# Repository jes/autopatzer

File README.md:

# autopatzer

An automatic chess board, supporting online play with people all over the world via the [Lichess Boards API](https://lichess.org/blog/XlRW5REAAB8AUJJ-/welcome-lichess-boards).

This repo contains FreeCAD files for the mechanical design, KiCad files for PCB design, Arduino code to run on
the microcontroller, Perl code for the library/program that interfaces with the controller, and JavaScript code for the
user interface and Lichess interface.

You can [watch a video of the board](https://www.youtube.com/watch?v=8ScFtkWvHW8) if you want.

## Build one yourself

I thoroughly encourage you to build an Autopatzer board. You'll need:

 - 3d printer
 - soldering skills
 - general DIY skills
 - and it would probably help to have prior experience with Arduino and Raspberry Pi

There aren't currently a decent set of instructions, so if you want to build one let's try and write some
instructions as you go so that it might be easier for whoever comes next!

There are some notes about how you might want to change the design in my blog post: https://incoherency.co.uk/blog/stories/autopatzer.html

## Architecture

There is a NEMA17 stepper motor for each of the X and Y axis, from an old 3d printer. The stepper motors are controlled by A4988 stepper
motor drivers, which are controlled using the step/direction pins, driven by the AccelStepper Arduino library. The electromagnet is switched
on and off with a MOSFET. The pieces are detected with an analogue hall effect sensor under each square. These 64 analogue signals are reduced
to 8 signals with 8x CD4051 8-to-1 analogue multiplexers. All of the code for this runs on a Teensy 3.2 microcontroller, and the rest is
adequately explained by this diagram:

## Contact

The Electron app providing the user interface is by Miles Armstrong: miles@milesarmstrong.co.uk

The rest is by James Stanley: james@incoherency.co.uk

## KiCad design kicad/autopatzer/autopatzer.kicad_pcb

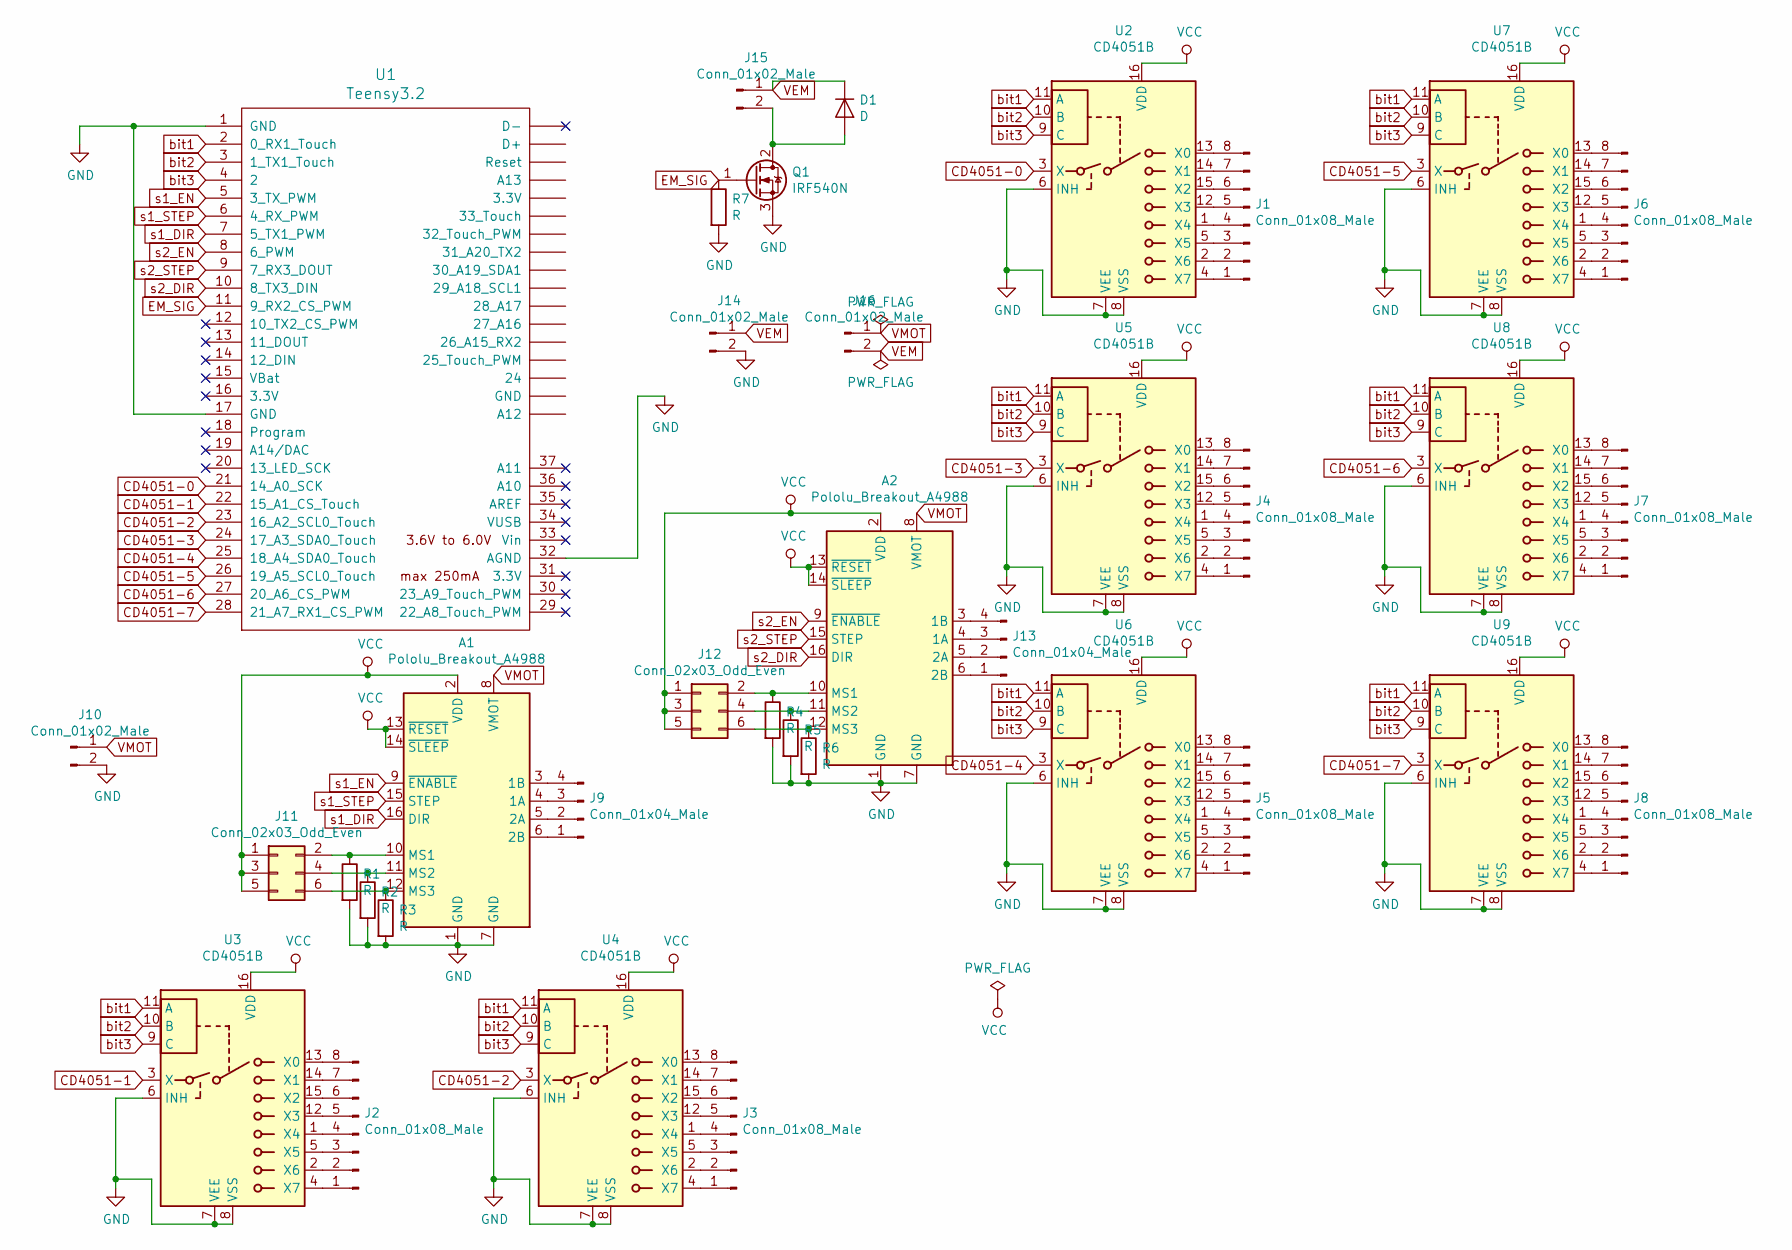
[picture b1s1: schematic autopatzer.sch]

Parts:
A1, A2: Pololu_Breakout_A4988; Pololu_Breakout-16_15.2x20.3mm
D1: D; D_5W_P12.70mm_Horizontal
J1, J2, J3, J4, J5, J6, J7, J8: Conn_01x08_Male; PinHeader_1x08_P2.54mm_Vertical
J9, J13: Conn_01x04_Male; PinHeader_1x04_P2.54mm_Vertical
J10, J14, J15, J16: Conn_01x02_Male; PinHeader_1x02_P2.54mm_Vertical
J11, J12: Conn_02x03_Odd_Even; PinHeader_2x03_P2.54mm_Vertical
Q1: IRF540N; TO-220-3_Vertical
R1, R2, R3, R4, R5, R6, R7: R; R_Axial_DIN0411_L9.9mm_D3.6mm_P12.70mm_Horizontal
U1: Teensy3.2; Teensy30_31_32_LC
U2, U3, U4, U5, U6, U7, U8, U9: CD4051B; DIP-16_W7.62mm

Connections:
CD4051-0: U1.21 (14_A0_SCK), U2.3 (X)
CD4051-1: U1.22 (15_A1_CS_Touch), U3.3 (X)
CD4051-2: U1.23 (16_A2_SCL0_Touch), U4.3 (X)
CD4051-3: U1.24 (17_A3_SDA0_Touch), U5.3 (X)
CD4051-4: U1.25 (18_A4_SDA0_Touch), U6.3 (X)
CD4051-5: U1.26 (19_A5_SCL0_Touch), U7.3 (X)
CD4051-6: U1.27 (20_A6_CS_PWM), U8.3 (X)
CD4051-7: U1.28 (21_A7_RX1_CS_PWM), U9.3 (X)
EM_SIG: Q1.1 (G), R7.1, U1.11 (9_RX2_CS_PWM)
GND: A1.1 (GND), A1.7 (GND), A2.1 (GND), A2.7 (GND), J10.2, J14.2, Q1.3 (S), R1.2, R2.2, R3.2, R4.2, R5.2, R6.2, R7.2, U1.1 (GND), U1.17 (GND), U1.32 (AGND), U2.6 (INH), U2.7 (VEE), U2.8 (VSS), U3.6 (INH), U3.7 (VEE), U3.8 (VSS), U4.6 (INH), U4.7 (VEE), U4.8 (VSS), U5.6 (INH), U5.7 (VEE), U5.8 (VSS), U6.6 (INH), U6.7 (VEE), U6.8 (VSS), U7.6 (INH), U7.7 (VEE), U7.8 (VSS), U8.6 (INH), U8.7 (VEE), U8.8 (VSS), U9.6 (INH), U9.7 (VEE), U9.8 (VSS)
unnamed: A1.3 (1B), J9.4
unnamed: A1.4 (1A), J9.3
unnamed: A1.5 (2A), J9.2
unnamed: A1.6 (2B), J9.1
unnamed: A1.10 (MS1), J11.2, R1.1
unnamed: A1.11 (MS2), J11.4, R2.1
unnamed: A1.12 (MS3), J11.6, R3.1
unnamed: A2.3 (1B), J13.4
unnamed: A2.4 (1A), J13.3
unnamed: A2.5 (2A), J13.2
unnamed: A2.6 (2B), J13.1
unnamed: A2.10 (MS1), J12.2, R4.1
unnamed: A2.11 (MS2), J12.4, R5.1
unnamed: A2.12 (MS3), J12.6, R6.1
unnamed: D1.2 (A), J15.2, Q1.2 (D)
unnamed: J1.1, U2.4 (X7)
unnamed: J1.2, U2.2 (X6)
unnamed: J1.3, U2.5 (X5)
unnamed: J1.4, U2.1 (X4)
unnamed: J1.5, U2.12 (X3)
unnamed: J1.6, U2.15 (X2)
unnamed: J1.7, U2.14 (X1)
unnamed: J1.8, U2.13 (X0)
unnamed: J2.1, U3.4 (X7)
unnamed: J2.2, U3.2 (X6)
unnamed: J2.3, U3.5 (X5)
unnamed: J2.4, U3.1 (X4)
unnamed: J2.5, U3.12 (X3)
unnamed: J2.6, U3.15 (X2)
unnamed: J2.7, U3.14 (X1)
unnamed: J2.8, U3.13 (X0)
unnamed: J3.1, U4.4 (X7)
unnamed: J3.2, U4.2 (X6)
unnamed: J3.3, U4.5 (X5)
unnamed: J3.4, U4.1 (X4)
unnamed: J3.5, U4.12 (X3)
unnamed: J3.6, U4.15 (X2)
unnamed: J3.7, U4.14 (X1)
unnamed: J3.8, U4.13 (X0)
unnamed: J4.1, U5.4 (X7)
unnamed: J4.2, U5.2 (X6)
unnamed: J4.3, U5.5 (X5)
unnamed: J4.4, U5.1 (X4)
unnamed: J4.5, U5.12 (X3)
unnamed: J4.6, U5.15 (X2)
unnamed: J4.7, U5.14 (X1)
unnamed: J4.8, U5.13 (X0)
unnamed: J5.1, U6.4 (X7)
unnamed: J5.2, U6.2 (X6)
unnamed: J5.3, U6.5 (X5)
unnamed: J5.4, U6.1 (X4)
unnamed: J5.5, U6.12 (X3)
unnamed: J5.6, U6.15 (X2)
unnamed: J5.7, U6.14 (X1)
unnamed: J5.8, U6.13 (X0)
unnamed: J6.1, U7.4 (X7)
unnamed: J6.2, U7.2 (X6)
unnamed: J6.3, U7.5 (X5)
unnamed: J6.4, U7.1 (X4)
unnamed: J6.5, U7.12 (X3)
unnamed: J6.6, U7.15 (X2)
unnamed: J6.7, U7.14 (X1)
unnamed: J6.8, U7.13 (X0)
unnamed: J7.1, U8.4 (X7)
unnamed: J7.2, U8.2 (X6)
unnamed: J7.3, U8.5 (X5)
unnamed: J7.4, U8.1 (X4)
unnamed: J7.5, U8.12 (X3)
unnamed: J7.6, U8.15 (X2)
unnamed: J7.7, U8.14 (X1)
unnamed: J7.8, U8.13 (X0)
unnamed: J8.1, U9.4 (X7)
unnamed: J8.2, U9.2 (X6)
unnamed: J8.3, U9.5 (X5)
unnamed: J8.4, U9.1 (X4)
unnamed: J8.5, U9.12 (X3)
unnamed: J8.6, U9.15 (X2)
unnamed: J8.7, U9.14 (X1)
unnamed: J8.8, U9.13 (X0)
VCC: A1.2 (VDD), A1.13 (~RESET), A1.14 (~SLEEP), A2.2 (VDD), A2.13 (~RESET), A2.14 (~SLEEP), J11.1, J11.3, J11.5, J12.1, J12.3, J12.5, U2.16 (VDD), U3.16 (VDD), U4.16 (VDD), U5.16 (VDD), U6.16 (VDD), U7.16 (VDD), U8.16 (VDD), U9.16 (VDD)
VEM: D1.1 (K), J14.1, J15.1, J16.2
VMOT: A1.8 (VMOT), A2.8 (VMOT), J10.1, J16.1
bit1: U1.2 (0_RX1_Touch), U2.11 (A), U3.11 (A), U4.11 (A), U5.11 (A), U6.11 (A), U7.11 (A), U8.11 (A), U9.11 (A)
bit2: U1.3 (1_TX1_Touch), U2.10 (B), U3.10 (B), U4.10 (B), U5.10 (B), U6.10 (B), U7.10 (B), U8.10 (B), U9.10 (B)
bit3: U1.4 (2), U2.9 (C), U3.9 (C), U4.9 (C), U5.9 (C), U6.9 (C), U7.9 (C), U8.9 (C), U9.9 (C)
s1_DIR: A1.16 (DIR), U1.7 (5_TX1_PWM)
s1_EN: A1.9 (~ENABLE), U1.5 (3_TX_PWM)
s1_STEP: A1.15 (STEP), U1.6 (4_RX_PWM)
s2_DIR: A2.16 (DIR), U1.10 (8_TX3_DIN)
s2_EN: A2.9 (~ENABLE), U1.8 (6_PWM)
s2_STEP: A2.15 (STEP), U1.9 (7_RX3_DOUT)

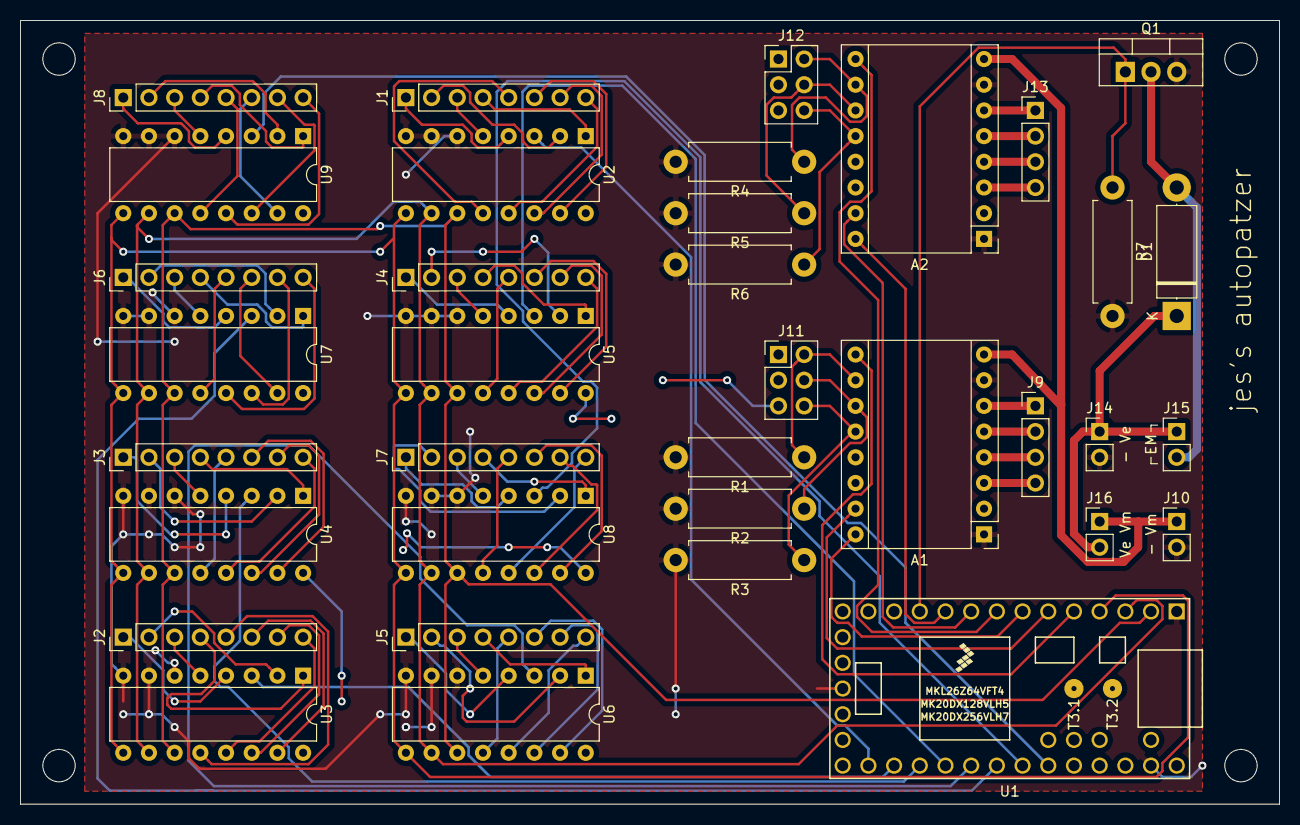
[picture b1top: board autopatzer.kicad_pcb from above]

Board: 2 copper layers, 124.5 x 77.5 mm, 36 parts (0 on the bottom side), 101 nets.

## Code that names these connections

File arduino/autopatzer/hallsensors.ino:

/* Hall sensor code for autopatzer
 *  
 * James Stanley 2020
 */

const int pieceSettleMs = 50; // don't report a square changed until it has settled for N ms

bool squareOccupied[64];
bool realSquareOccupied[64];
unsigned long lastChange[64];

// map sensor locations to actual squares (0=a1, 7=a8, 8=b1, 56=h1, 63=h8)
int squareMap[64] = {
  36, 29, 18, 43, 59, 12, 49,  4,
  32, 31, 21, 45, 61, 15, 52,  0,
  34, 26, 20, 42, 56,  9, 54,  2,
  38, 24, 16, 44, 60, 11, 50,  5,
  35, 27, 17, 40, 58, 10, 53,  7,
  37, 30, 19, 47, 63, 13, 55,  6,
  39, 28, 23, 46, 62,  8, 51,  3,
  33, 25, 22, 41, 57, 14, 48,  1,
};

// we set a different threshold for each square
int analogThreshold[64] = {
//  1    2    3    4    5    6    7    8
  715, 745, 695, 705, 690, 650, 690, 730, // a
  715, 680, 715, 735, 675, 725, 675, 730, // b
  740, 705, 695, 655, 680, 710, 730, 715, // c
  720, 690, 740, 720, 705, 690, 640, 715, // d
  710, 755, 670, 695, 640, 710, 715, 750, // e
  700, 745, 675, 705, 725, 690, 715, 705, // f
  660, 700, 630, 645, 710, 725, 720, 725, // g
  725, 675, 690, 680, 720, 675, 680, 710, // h
};

int bit1pin, bit2pin, bit3pin;

void initHallSensors(int bit1, int bit2, int bit3) {
  bit1pin = bit1;
  bit2pin = bit2;
  bit3pin = bit3;
  pinMode(bit1, OUTPUT);
  pinMode(bit2, OUTPUT);
  pinMode(bit3, OUTPUT);

  scanHallSensors();
  for (int i = 0; i < 64; i++)
    realSquareOccupied[i] = squareOccupied[i];
}

void waitHallSensors(int ms) {
  unsigned long start = millis();

  while (millis() < start+ms) {
    updateHallSensors();
  }
}

void updateHallSensors() {
  scanHallSensors();
  for (int i = 0; i < 64; i++) {
    if (millis() - lastChange[i] > pieceSettleMs && squareOccupied[i] != realSquareOccupied[i]) {
      realSquareOccupied[i] = squareOccupied[i];
      if (realSquareOccupied[i] ) {
        Serial.print("piecedown "); Serial.println(square2Name(i));
      } else {
        Serial.print("pieceup "); Serial.println(square2Name(i));
      }
    }
  }
}

void scanHallSensors() {
  for (int i = 0; i < 8; i++) {
    digitalWrite(bit1pin, i&1);
    digitalWrite(bit2pin, i&2);
    digitalWrite(bit3pin, i&4);
    // XXX: do we need to wait between writing to the bit pins and reading from the analogue pins?
    for (int j = 0; j < 8; j++) {
      updateSteppers(); // HACK: don't let scanHallSensors() block stepper motor operation
      int sqr = squareMap[i*8+j];
      int val = analogRead(j);
      bool occ = val > (analogThreshold[sqr] + 35);
      if (squareOccupied[sqr] != occ) {
        squareOccupied[sqr] = occ;
        lastChange[sqr] = millis();
      }
    }
  }
}

void analogScanHallSensors() {
  int maxRead[64];
  for (int i = 0; i < 64; i++)
    maxRead[i] = 0;
  for (int n = 0; n < 100; n++) {
  for (int i = 0; i < 8; i++) {
    digitalWrite(bit1pin, i&1);
    digitalWrite(bit2pin, i&2);
    digitalWrite(bit3pin, i&4);
    // XXX: do we need to wait between writing to the bit pins and reading from the analogue pins?
    for (int j = 0; j < 8; j++) {
      int sqr = squareMap[i*8+j];
      int val = analogRead(j);
      if (val > maxRead[sqr])
        maxRead[sqr] = val;
    }
  }
  delay(10);
  }

  for (int i = 0; i < 64; i++) {
    Serial.print(i); Serial.print(" = "); Serial.print(maxRead[i]); Serial.print("; ");
    if (i % 8 == 7)
      Serial.print("\n");
  }
}

// XXX: returns pointer to static buffer
char *square2Name(int square) {
  static char s[3];
  
  if (square < 0 || square > 63) {
    s[0] = 'x'; s[1] = 'x'; s[2] = 0;
    return s;
  }

  s[0] = (square/8) + 'a';
  s[1] = (square%8) + '1';
  s[2] = 0;
  return s;
}

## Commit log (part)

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2020-03-03 Add xbracket-idler
2020-03-03 Add xbracket-stepper
2020-03-05 Add electromagnet, top part of carriage, NEMA17 stepper
2020-03-06 Add ybracket-stepper
2020-03-23 Update CAD model
2020-03-23 Add KiCad project
2020-03-23 Track piece up/down, disable magnet if it is left on for too long
2020-03-23 Add initial CLI
2020-03-24 Improve serial output
2020-03-25 Understand capture inputs from the board
2020-03-25 Simple captures when moving motors
2020-03-26 Fix routing in shortest path
2020-03-26 Clarify
2020-03-26 Tidy up
2020-03-26 Play Stockfish
2020-03-26 More generalised graph search, to facilitate moving pieces out of the way
2020-03-27 Support castling
2020-04-04 Move magnet code into separate file, set per-square hall sensor threshold, add electromagnetic homing
    The EM homing doesn't work properly so is currently disabled, and in practice I don't think it can
    work very well most of the time anyway.
2020-04-04 Nerf stockfish, auto-adjust pieces if they're not on the starting squares
    In future this should also adjust pieces after every computer move if we detect they've gone missing.
2020-04-11 Fix syntax
2020-04-11 Implement pawn promotion, improve movement cost estimation (queen-only)
2020-04-11 Always do a large movement instead of 2 small ones in the same direction
2020-04-12 Depend on installed stockfish
2020-04-12 Move freecad files into freecad/
2020-04-25 Rename directories
2020-04-25 Add API.md
2020-04-25 What to do if not starting position
2020-04-25 Add reset message
2020-04-25 Listen on port 3001
2020-04-27 autopatzerd => mock-autopatzerd
2020-04-27 Copy stdio-websocket from isopath project
2020-04-27 Document ping
2020-04-27 Send ping, improve error message
2020-04-27 Add Autopatzer->reset, stop trying to adjust the pieces at startup
2020-04-27 Add skeleton of autopatzerd
2020-04-30 Remove node_modules
2020-04-30 Use create-react-app with electron
2020-04-30 Depend on yarn
2020-04-30 Things:
    Moves list autoscrolling
    Moves converted to PGN
    Timers
2020-05-01 Add Dockerfile
2020-05-02 Allow starting existing game, or start 'found' game
2020-05-02 Use AnyEvent instead of Mojo::IOLoop::Stream
2020-05-02 Send board changes to websocket clients
2020-05-02 Check occupied on board rather than in game
2020-05-02 Monitor interrupts with Python instead of Perl
2020-05-02 Fix typo
2020-05-04 Don't move a piece if it isn't there
2020-05-04 Split out piece-routing into Autopatzer::Router, with unit test
2020-05-04 Do the websockets
2020-05-04 The ping should be JSON
2020-05-05 Use object method properly
2020-05-05 20% performance gain
2020-05-05 Add minimum path cost to priority queue insertion
    The old version was mainly so slow because it was spending lots of time
    considering various piece displacements nearby, because they are short
    movements and come up first in the queue. Instead of ordering by the
    path length *so far*, we should order the queue by the minimum path length
    to the end state.
    I guess this is now more A* than Dijkstra?
2020-05-05 Increase thresholds again
2020-05-05 Document 'moves' in op:reset
2020-05-05 Fix logic about whose move it is
2020-05-05 Play through moves from reset message
2020-05-05 Use winston for logging
2020-05-07 Handle pawn promotion
2020-05-07 Stop timers if game has ended
2020-05-07 Allow resuming in-progress games by sending move history with op:reset
2020-05-07 Fix some errors and warnings
2020-05-07 Log messages sent and received
2020-05-07 Fix filename
2020-05-07 Show player name instead of id
2020-05-07 Hide pawn promotion modal unless we explicitly want to show it
2020-05-07 Fix promotion to non-queens
2020-05-08 Bump thresholds again (lol)
2020-05-08 Improve existing games list
2020-05-08 Add rated to seek game options
2020-05-09 Revert "Optionally hide cursor"
    This reverts commit 9c798fac35fba8dd7b0671d142cd4a55f64cf017.
    Doesn't work: the cursor is hidden initially, but anything that touches
    the cursor then brings it back, because React doesn't know.
2020-05-09 Show IP address on home screen
2020-05-09 Auto-refresh in-progress games
2020-05-09 Fit IP address on screen when there are games in progress
2020-05-09 Show current games in progress immediately, without waiting for timer to fire
2020-05-09 Refactor some components
2020-05-09 Start on design for Game view
2020-05-09 Bring back refreshing of in-progress games (lost in rebase)
2020-05-09 Display No Existing Games if none in progress
2020-05-09 Update player online status immediately before starting interval update
2020-05-09 Fix typo for logfiles
2020-05-09 Moves list styling
2020-05-09 Just show move text, and remove CONFIRM
2020-05-09 Add power off button (but right justify is not working)
2020-05-09 Wiggle the motors to wake the user up if he is to move at the start of the game
2020-05-09 Make better use of space in move history
2020-05-09 eqeqeq
2020-05-10 Untested en-passant input detection
2020-05-10 Split out input detection into a separate module
2020-05-10 setBoardChanges with the on-screen confirm button, and fix React warnings about missing dependencies
2020-05-10 Set board changes when using the on-screen button
2020-05-10 Log lichess-make-move
2020-05-10 Create custom hooks for the event streams
2020-05-10 Fix all hook dependency warnings
2020-05-10 Reset autopatzerdMove as soon as the move is sent off to lichess
2020-05-10 (Untested) Return undefined instead of crashing if illegal move
2020-05-11 Make writing better
2020-05-11 Make confirm move button text bigger
2020-05-11 Make gained/lost a bit smaller
2020-05-11 Implement leave/draw/resign
2020-05-11 Fix blunder
2020-05-12 Fix glitchy clocks
2020-05-12 Adjust e4,f5 thresholds
2020-05-12 Confirmation of poweroff
2020-05-12 Fix sweetalert title
2020-05-12 Write an initial blank line to the Teensy
2020-05-12 Get IP address at start as well as on interval
2020-05-12 Prettier has done lots of reformatting
2020-05-12 Remove useEffect dependency on autopatzerdMove (maybe causing infinite loop?)
2020-05-12 Fix infinite loop
2020-05-12 Move closures out of clock object
2020-05-13 Update d5 threshold
2020-05-13 Grid layout of BoardChanges and ConfirmMove
2020-05-13 We only render result component if gameOver, don't need to pass it in
2020-05-13 Add README.md
2020-05-13 Add images
2020-05-13 Don't need a button if no move
2020-05-13 Light grey backlground
2020-05-21 Don't let clock tick below 0
2020-07-07 Bump electron from 8.2.3 to 8.2.4 in /electron
    Bumps [electron](https://github.com/electron/electron) from 8.2.3 to 8.2.4.
    - [Release notes](https://github.com/electron/electron/releases)
    - [Changelog](https://github.com/electron/electron/blob/master/docs/breaking-changes.md)
    - [Commits](https://github.com/electron/electron/compare/v8.2.3...v8.2.4)
2020-08-01 Bump elliptic from 6.5.2 to 6.5.3 in /electron
    Bumps [elliptic](https://github.com/indutny/elliptic) from 6.5.2 to 6.5.3.
    - [Release notes](https://github.com/indutny/elliptic/releases)
    - [Commits](https://github.com/indutny/elliptic/compare/v6.5.2...v6.5.3)
2020-10-06 Bump electron from 8.2.3 to 8.5.1 in /electron
    Bumps [electron](https://github.com/electron/electron) from 8.2.3 to 8.5.1.
    - [Release notes](https://github.com/electron/electron/releases)
    - [Changelog](https://github.com/electron/electron/blob/master/docs/breaking-changes.md)
    - [Commits](https://github.com/electron/electron/compare/v8.2.3...v8.5.1)
2020-10-06 Bump electron from 8.2.3 to 8.5.2 in /electron
    Bumps [electron](https://github.com/electron/electron) from 8.2.3 to 8.5.2.
    - [Release notes](https://github.com/electron/electron/releases)
    - [Changelog](https://github.com/electron/electron/blob/master/docs/breaking-changes.md)
    - [Commits](https://github.com/electron/electron/compare/v8.2.3...v8.5.2)
2021-03-10 Bump elliptic from 6.5.2 to 6.5.4 in /electron
    Bumps [elliptic](https://github.com/indutny/elliptic) from 6.5.2 to 6.5.4.
    - [Release notes](https://github.com/indutny/elliptic/releases)
    - [Commits](https://github.com/indutny/elliptic/compare/v6.5.2...v6.5.4)
2021-05-09 Bump url-parse from 1.4.7 to 1.5.1 in /electron
    Bumps [url-parse](https://github.com/unshiftio/url-parse) from 1.4.7 to 1.5.1.
    - [Release notes](https://github.com/unshiftio/url-parse/releases)
    - [Commits](https://github.com/unshiftio/url-parse/compare/1.4.7...1.5.1)
2021-05-11 Bump hosted-git-info from 2.8.8 to 2.8.9 in /electron
    Bumps [hosted-git-info](https://github.com/npm/hosted-git-info) from 2.8.8 to 2.8.9.
    - [Release notes](https://github.com/npm/hosted-git-info/releases)
    - [Changelog](https://github.com/npm/hosted-git-info/blob/v2.8.9/CHANGELOG.md)
    - [Commits](https://github.com/npm/hosted-git-info/compare/v2.8.8...v2.8.9)
2021-06-08 Bump merge-deep from 3.0.2 to 3.0.3 in /electron
    Bumps [merge-deep](https://github.com/jonschlinkert/merge-deep) from 3.0.2 to 3.0.3.
    - [Release notes](https://github.com/jonschlinkert/merge-deep/releases)
    - [Commits](https://github.com/jonschlinkert/merge-deep/compare/3.0.2...3.0.3)
    ---
    updated-dependencies:
    - dependency-name: merge-deep
2021-08-12 Bump path-parse from 1.0.6 to 1.0.7 in /electron
    Bumps [path-parse](https://github.com/jbgutierrez/path-parse) from 1.0.6 to 1.0.7.
    - [Release notes](https://github.com/jbgutierrez/path-parse/releases)
    - [Commits](https://github.com/jbgutierrez/path-parse/commits/v1.0.7)
    ---
    updated-dependencies:
    - dependency-name: path-parse
2021-10-06 Bump url-parse from 1.4.7 to 1.5.3 in /electron
    Bumps [url-parse](https://github.com/unshiftio/url-parse) from 1.4.7 to 1.5.3.
    - [Release notes](https://github.com/unshiftio/url-parse/releases)
    - [Commits](https://github.com/unshiftio/url-parse/compare/1.4.7...1.5.3)
    ---
    updated-dependencies:
    - dependency-name: url-parse
2022-01-14 Bump follow-redirects from 1.10.0 to 1.14.7 in /electron
    Bumps [follow-redirects](https://github.com/follow-redirects/follow-redirects) from 1.10.0 to 1.14.7.
    - [Release notes](https://github.com/follow-redirects/follow-redirects/releases)
    - [Commits](https://github.com/follow-redirects/follow-redirects/compare/v1.10.0...v1.14.7)
    ---
    updated-dependencies:
    - dependency-name: follow-redirects
2022-02-13 Bump ajv from 6.12.0 to 6.12.6 in /electron
    Bumps [ajv](https://github.com/ajv-validator/ajv) from 6.12.0 to 6.12.6.
    - [Release notes](https://github.com/ajv-validator/ajv/releases)
    - [Commits](https://github.com/ajv-validator/ajv/compare/v6.12.0...v6.12.6)
    ---
    updated-dependencies:
    - dependency-name: ajv
2022-02-19 Bump url-parse from 1.4.7 to 1.5.7 in /electron
    Bumps [url-parse](https://github.com/unshiftio/url-parse) from 1.4.7 to 1.5.7.
    - [Release notes](https://github.com/unshiftio/url-parse/releases)
    - [Commits](https://github.com/unshiftio/url-parse/compare/1.4.7...1.5.7)
    ---
    updated-dependencies:
    - dependency-name: url-parse
2022-02-27 Bump url-parse from 1.4.7 to 1.5.10 in /electron
    Bumps [url-parse](https://github.com/unshiftio/url-parse) from 1.4.7 to 1.5.10.
    - [Release notes](https://github.com/unshiftio/url-parse/releases)
    - [Commits](https://github.com/unshiftio/url-parse/compare/1.4.7...1.5.10)
    ---
    updated-dependencies:
    - dependency-name: url-parse
2022-04-29 Bump async from 2.6.3 to 2.6.4 in /electron
    Bumps [async](https://github.com/caolan/async) from 2.6.3 to 2.6.4.
    - [Release notes](https://github.com/caolan/async/releases)
    - [Changelog](https://github.com/caolan/async/blob/v2.6.4/CHANGELOG.md)
    - [Commits](https://github.com/caolan/async/compare/v2.6.3...v2.6.4)
    ---
    updated-dependencies:
